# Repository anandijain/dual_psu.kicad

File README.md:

# diy modular synth in kicad

watch the video series where i build this!

https://www.youtube.com/playlist?list=PL79kqjVnD2ENdJDDSTUD3ZMdZPhVVu8yw

- psu completed, ready to print
- vca (needs to be redone)
- vco 

# todo
- vcf 
- envelope generator

build notes

* for the m2 standoffs i got, use 1/8 in holes and use the m3x12 screws into the acryllic and there is no need to countersink 
* to mount pots to the acryllic, drill 9/32 " holes 
* for 1/4" jack sockets use 3/8" holes

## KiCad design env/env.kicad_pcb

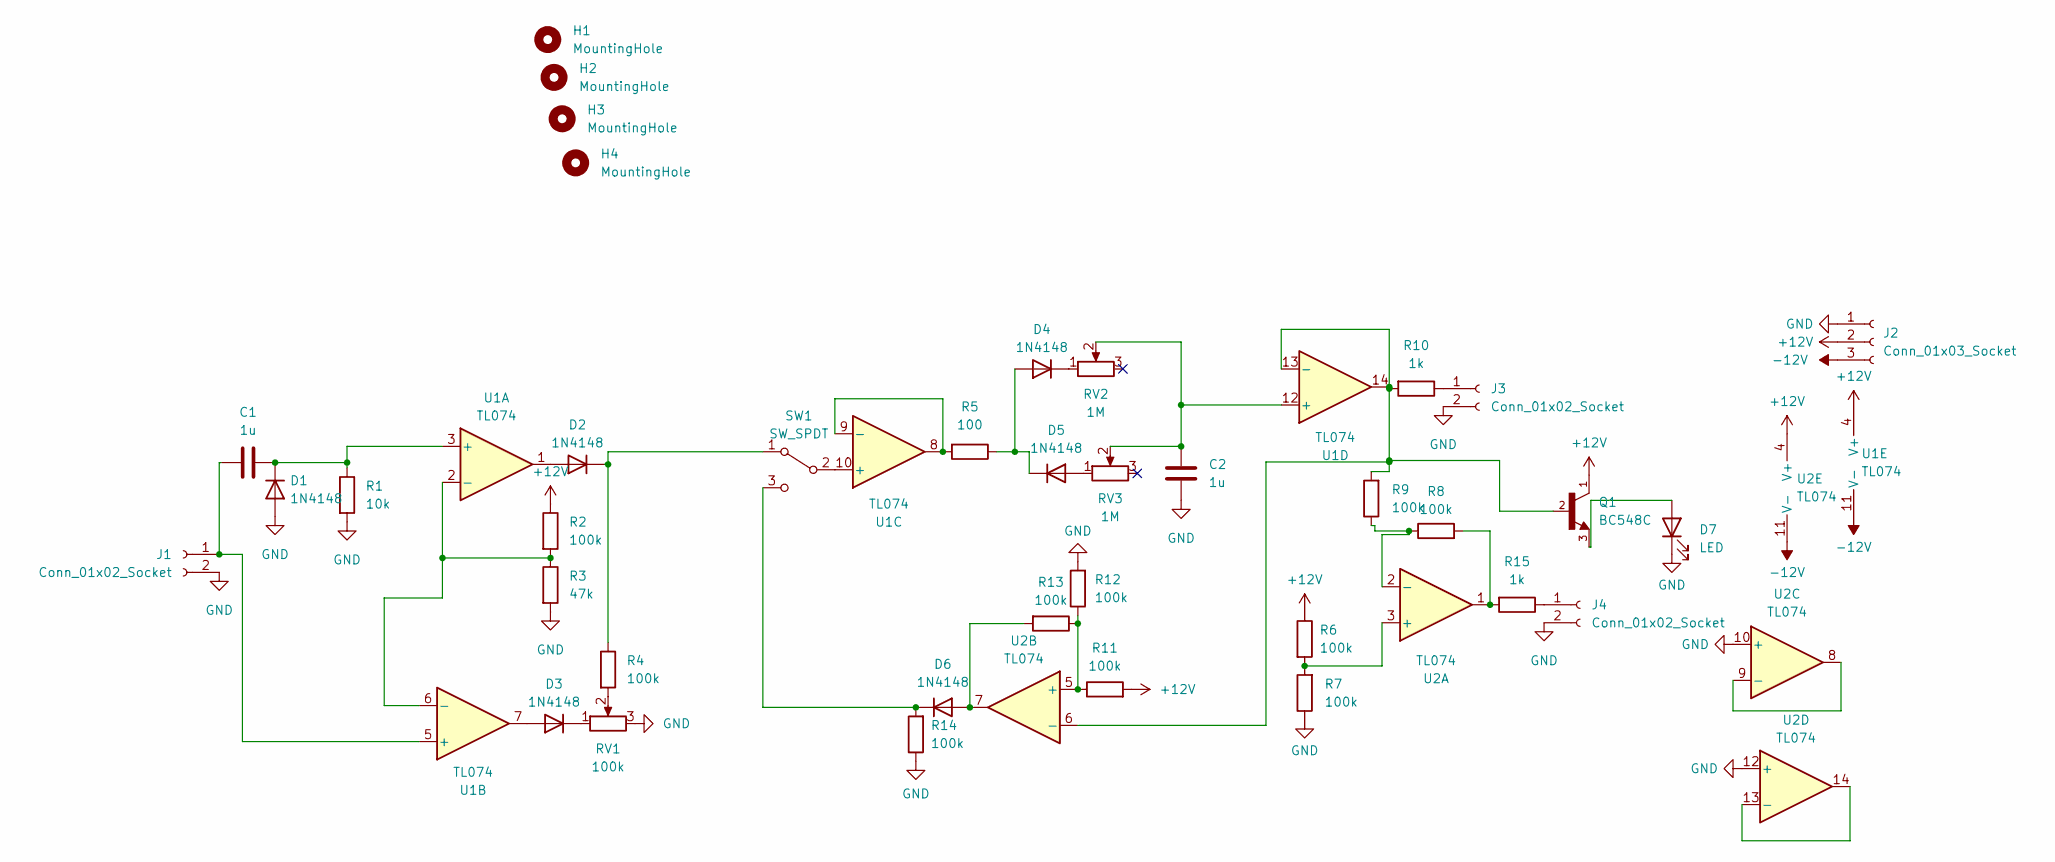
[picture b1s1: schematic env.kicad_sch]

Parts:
C1, C2: 1u; my_tht_cap
D1, D2, D3, D4, D5, D6: 1N4148; my_tht_diode
D7: LED; LED_D3.0mm
H1, H2, H3, H4: MountingHole; MountingHole_2.1mm
J1, J3, J4: Conn_01x02_Socket; my_really_cool_2pin
J2: Conn_01x03_Socket; my_really_cool_3pin
Q1: BC548C; my_bc548
R1: 10k; my_tht_r
R2, R4, R6, R7, R8, R9, R11, R12, R13, R14: 100k; my_tht_r
R3: 47k; my_tht_r
R5: 100; my_tht_r
R10, R15: 1k; my_tht_r
RV1: 100k; my_really_cool_3pin
RV2, RV3: 1M; my_really_cool_2pin
SW1: SW_SPDT; my_really_cool_3pin
U1, U2: TL074; my_dip14_no_f_pads

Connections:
+12V: J2.2, Q1.1, R2.1, R6.1, R11.2, U1.4 (V+), U2.4 (V+)
-12V: J2.3, U1.11 (V-), U2.11 (V-)
GND: C2.1, D1.2 (A), D7.1 (K), J1.2, J2.1, J3.2, J4.2, R1.2, R3.2, R7.1, R12.2, R14.1, RV1.3, U2.10 (+), U2.12 (+)
unnamed: C1.2, D1.1 (K), R1.1, U1.3 (+)
unnamed: D2.2 (A), U1.1
unnamed: D2.1 (K), R4.1, SW1.1 (A)
unnamed: D3.2 (A), U1.7
unnamed: D3.1 (K), RV1.1
unnamed: D4.2 (A), D5.1 (K), R5.1
unnamed: D4.1 (K), RV2.1
unnamed: D5.2 (A), RV3.1
unnamed: D6.2 (A), R13.2, U2.7
unnamed: D6.1 (K), R14.2, SW1.3 (C)
unnamed: D7.2 (A), Q1.3
unnamed: C1.1, J1.1, U1.5 (+)
unnamed: J3.1, R10.1
unnamed: J4.1, R15.1
unnamed: R4.2, RV1.2
unnamed: R8.2, R15.2, U2.1
unnamed: SW1.2 (B), U1.10 (+)
unnamed: R2.2, R3.1, U1.2 (-), U1.6 (-)
unnamed: R5.2, U1.8, U1.9 (-)
unnamed: C2.2, RV2.2, RV3.2, U1.12 (+)
unnamed: Q1.2, R9.2, R10.2, U1.13 (-), U1.14, U2.6 (-)
unnamed: R6.2, R7.2, U2.3 (+)
unnamed: R8.1, R9.1, U2.2 (-)
unnamed: R11.1, R12.1, R13.1, U2.5 (+)
unnamed: U2.8, U2.9 (-)
unnamed: U2.13 (-), U2.14

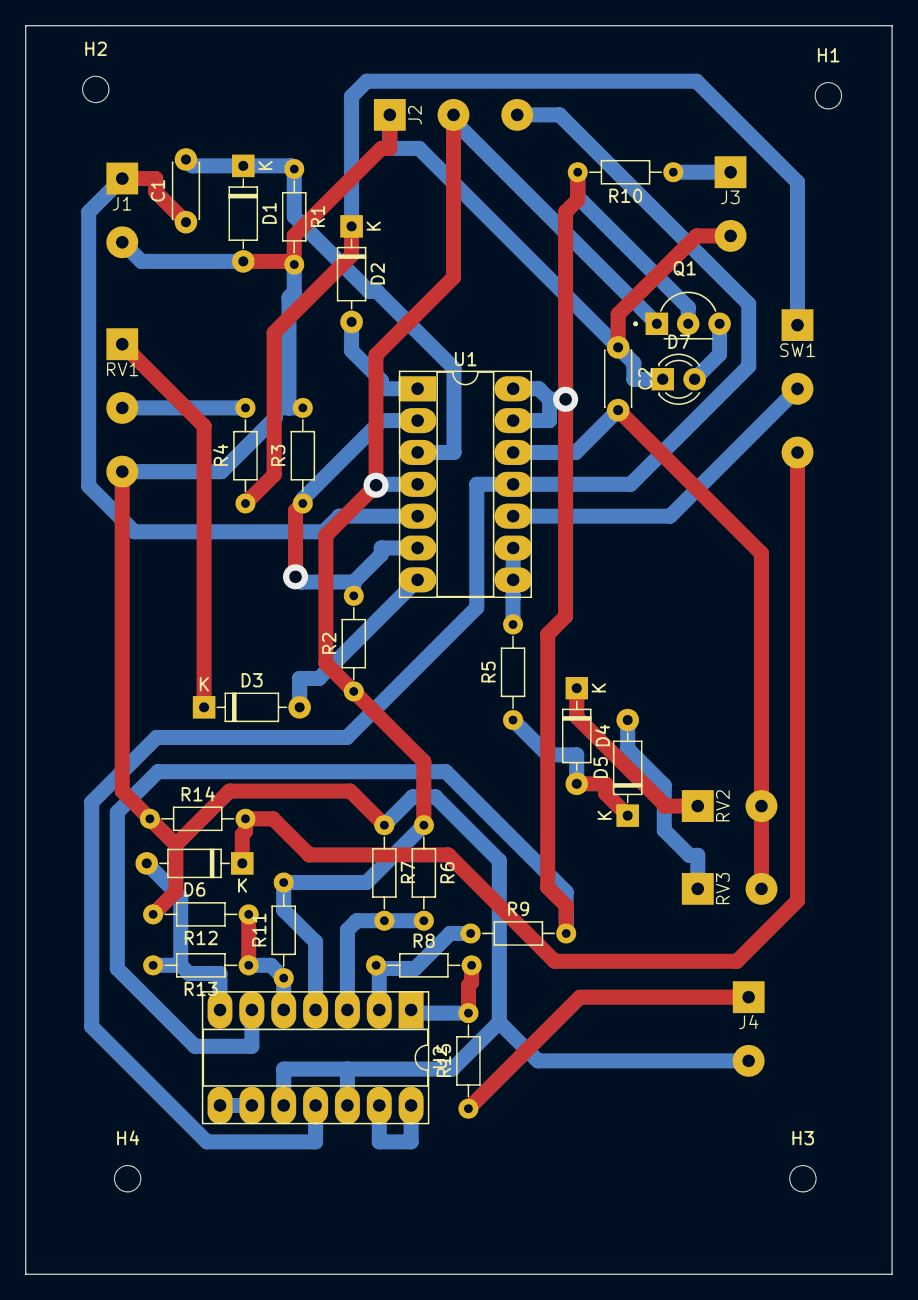
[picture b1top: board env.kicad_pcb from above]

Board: 2 copper layers, 69.1 x 99.6 mm, 39 parts (0 on the bottom side), 29 nets.

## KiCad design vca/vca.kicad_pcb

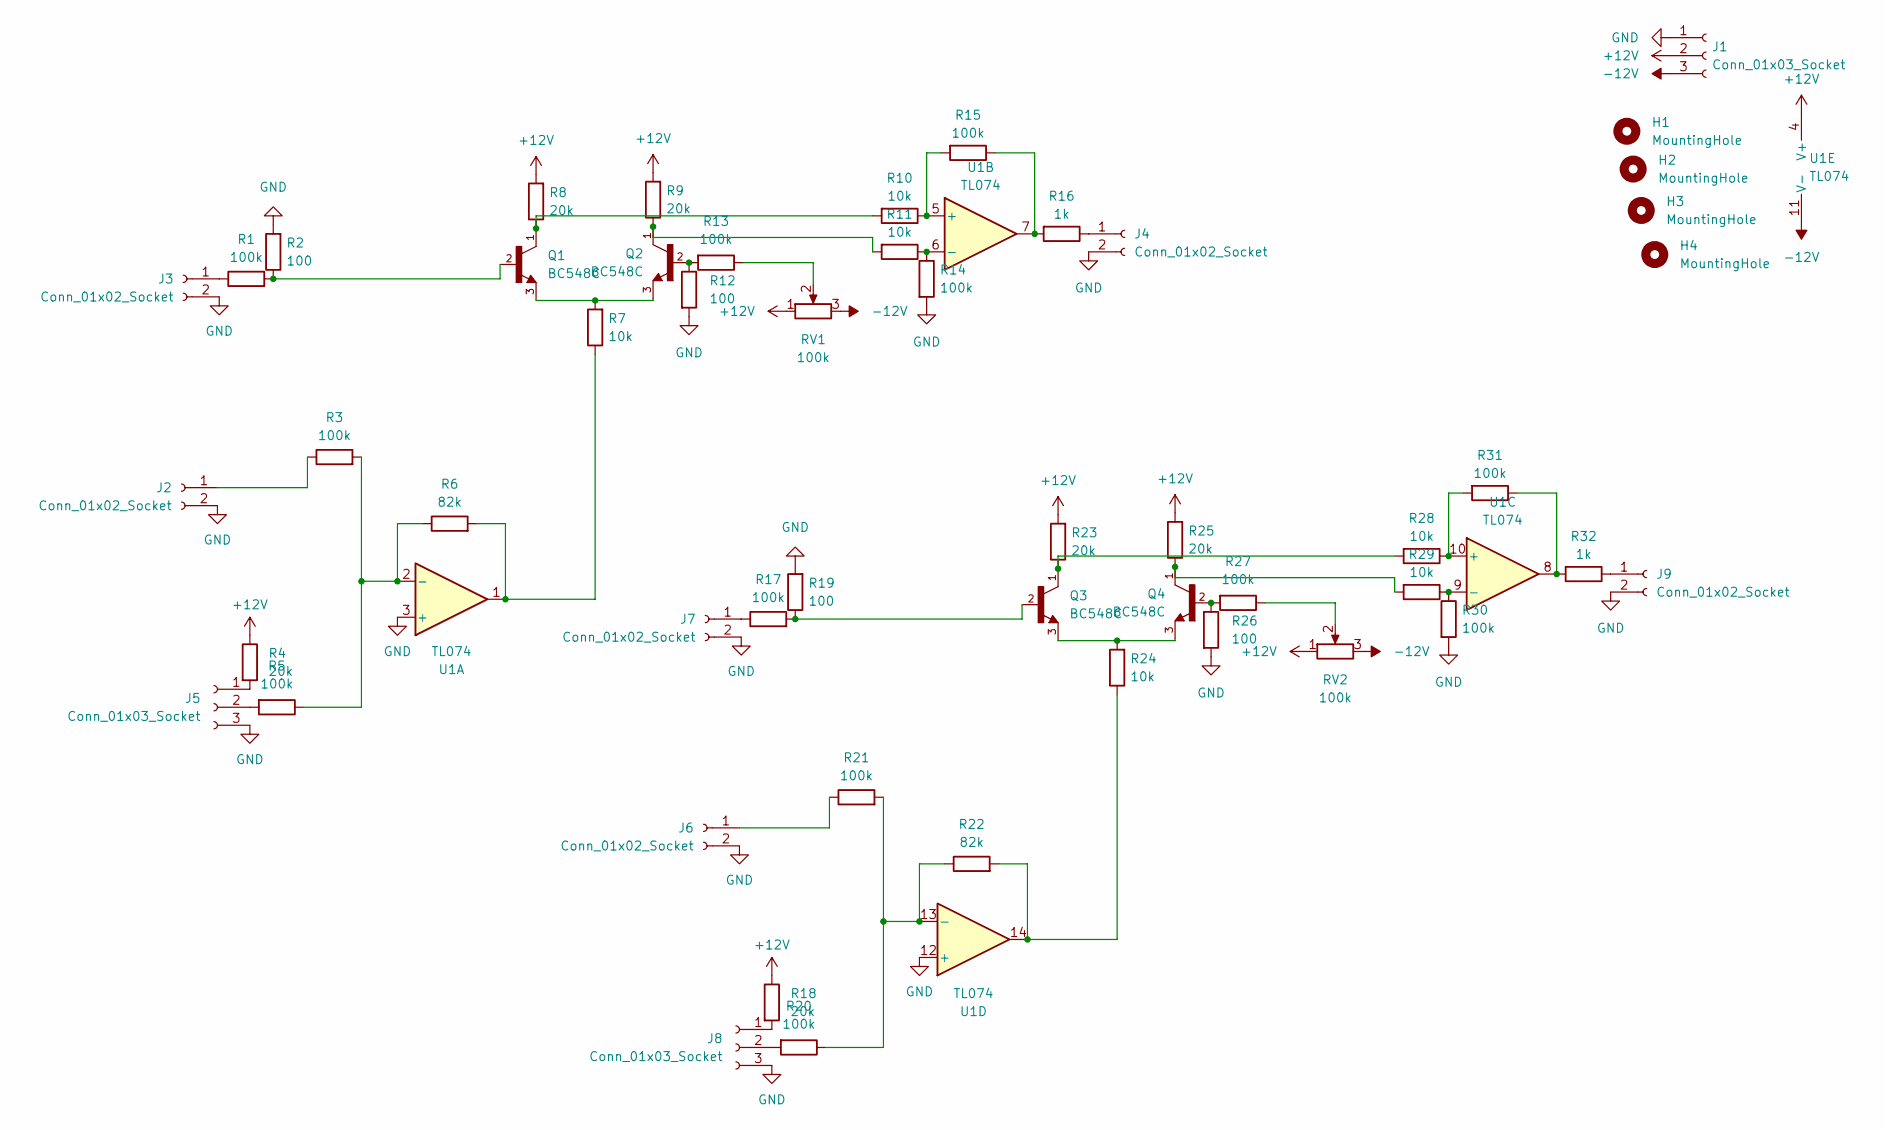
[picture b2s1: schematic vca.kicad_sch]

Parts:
H1, H2, H3, H4: MountingHole; MountingHole_2.1mm
J1, J5, J8: Conn_01x03_Socket; my_really_cool_3pin
J2, J3, J4, J6, J7, J9: Conn_01x02_Socket; my_really_cool_2pin
Q1, Q2, Q3, Q4: BC548C; my_bc548
R1, R3, R5, R13, R14, R15, R17, R20, R21, R27, R30, R31: 100k; my_tht_r
R2, R12, R19, R26: 100; my_tht_r
R4, R8, R9, R18, R23, R25: 20k; my_tht_r
R6, R22: 82k; my_tht_r
R7, R10, R11, R24, R28, R29: 10k; my_tht_r
R16, R32: 1k; my_tht_r
RV1, RV2: 100k; my_trimmer
U1: TL074; my_dip14_no_f_pads

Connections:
+12V: J1.2, R4.1, R8.2, R9.2, R18.1, R23.2, R25.2, RV1.1, RV2.1, U1.4 (V+)
-12V: J1.3, RV1.3, RV2.3, U1.11 (V-)
GND: J1.1, J2.2, J3.2, J4.2, J5.3, J6.2, J7.2, J8.3, J9.2, R2.2, R12.2, R14.2, R19.2, R26.2, R30.2, U1.3 (+), U1.12 (+)
unnamed: J2.1, R3.1
unnamed: J3.1, R1.1
unnamed: J4.1, R16.1
unnamed: J5.1, R4.2
unnamed: J5.2, R5.2
unnamed: J6.1, R21.1
unnamed: J7.1, R17.1
unnamed: J8.1, R18.2
unnamed: J8.2, R20.2
unnamed: J9.1, R32.1
unnamed: Q1.1, R8.1, R10.2
unnamed: Q1.2, R1.2, R2.1
unnamed: Q1.3, Q2.3, R7.2
unnamed: Q2.1, R9.1, R11.2
unnamed: Q2.2, R12.1, R13.2
unnamed: Q3.1, R23.1, R28.2
unnamed: Q3.2, R17.2, R19.1
unnamed: Q3.3, Q4.3, R24.2
unnamed: Q4.1, R25.1, R29.2
unnamed: Q4.2, R26.1, R27.2
unnamed: R6.2, R7.1, U1.1
unnamed: R13.1, RV1.2
unnamed: R15.1, R16.2, U1.7
unnamed: R22.2, R24.1, U1.14
unnamed: R27.1, RV2.2
unnamed: R31.1, R32.2, U1.8
unnamed: R3.2, R5.1, R6.1, U1.2 (-)
unnamed: R10.1, R15.2, U1.5 (+)
unnamed: R11.1, R14.1, U1.6 (-)
unnamed: R28.1, R31.2, U1.10 (+)
unnamed: R29.1, R30.1, U1.9 (-)
unnamed: R20.1, R21.2, R22.1, U1.13 (-)

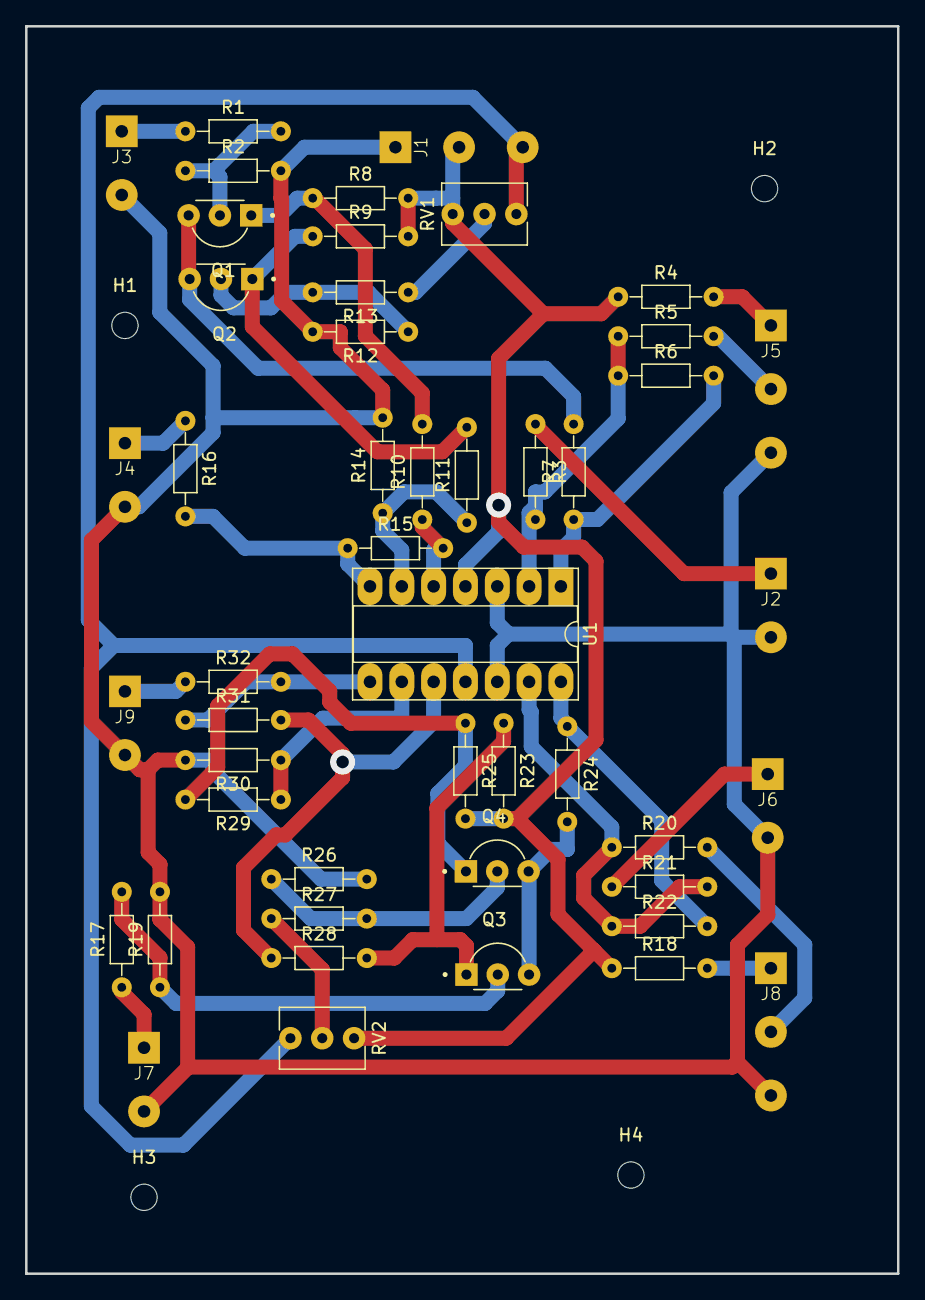
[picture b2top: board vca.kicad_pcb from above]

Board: 2 copper layers, 69.6 x 99.6 mm, 52 parts (0 on the bottom side), 35 nets.

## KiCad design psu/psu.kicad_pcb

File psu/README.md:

# psu.kicad

basic +-12v dual power supply from 12vac

designed to be done diy with ferric chloride (thick traces)

## Parts
- big caps https://www.amazon.com/dp/B08KTLQLVK
- -12v regulator https://www.digikey.com/en/products/detail/stmicroelectronics/L7912CV/585997
- +12v regulator https://www.digikey.com/en/products/detail/stmicroelectronics/L7812CV/585973
- diodes https://www.amazon.com/gp/product/B07Q5FZR7X
- small caps https://www.amazon.com/gp/product/B094HRK8QX/
- copper boards https://www.amazon.com/dp/B01MCVLDDZ

00:00:00 intro/materials
00:07:30 buffing board
00:10:00 tracing 
00:26:30 etching
00:42:30 rinse
01:01:00 how to not dremel
01:22:00 drilling
01:39:55 soldering

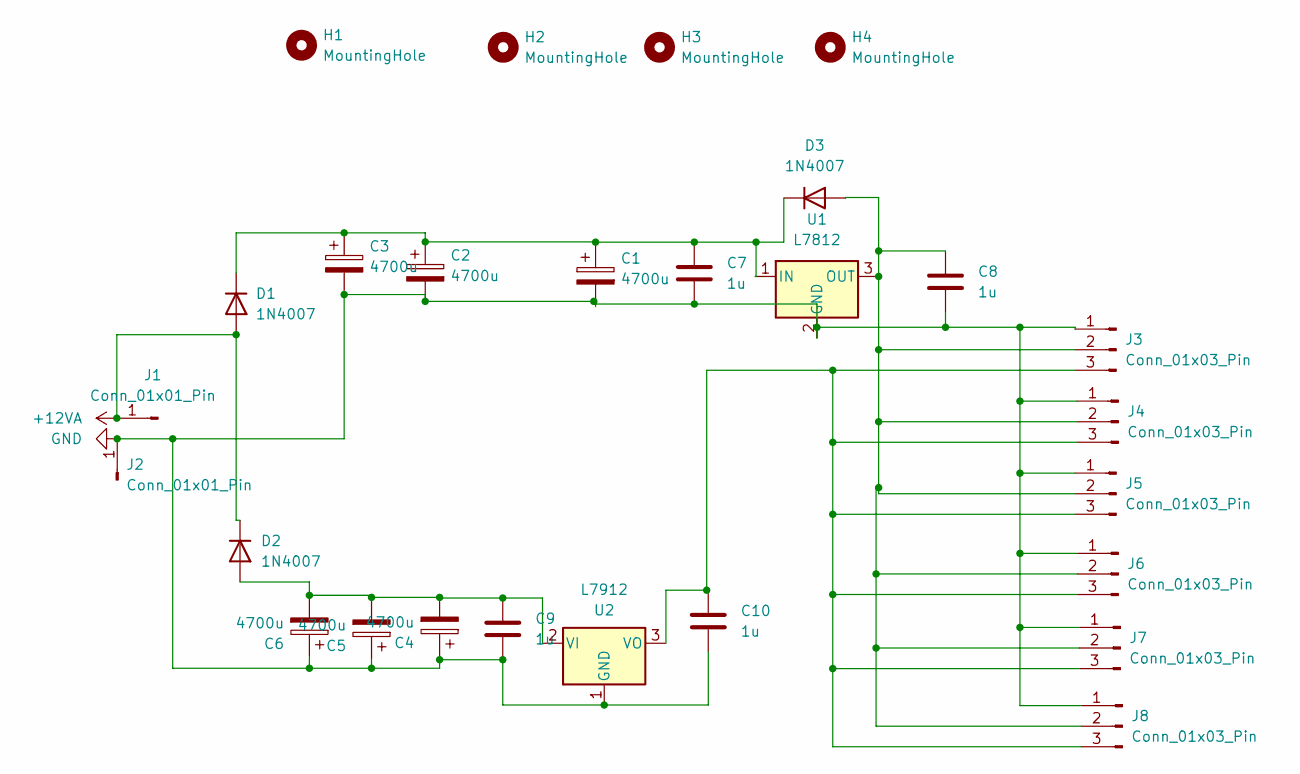
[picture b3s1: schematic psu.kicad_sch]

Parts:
C1, C2, C3, C4, C5, C6: 4700u; C_Radial_D18.0mm_H35.5mm_P7.50mm
C7, C8, C9, C10: 1u; C_Disc_D4.3mm_W1.9mm_P5.00mm
D1, D2, D3: 1N4007; D_DO-41_SOD81_P10.16mm_Horizontal
H1, H2, H3, H4: MountingHole; MountingHole_2.5mm
J1, J2: Conn_01x01_Pin; PinHeader_1x01_P2.54mm_Vertical
J3, J4, J5, J6, J7, J8: Conn_01x03_Pin; PinHeader_1x03_P2.54mm_Vertical
U1: L7812; TO-220-3_Vertical
U2: L7912; TO-220-3_Vertical

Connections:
+12VA: D1.2 (A), D2.1 (K), J1.1
GND: C1.2, C2.2, C3.2, C4.1, C5.1, C6.1, C7.2, C8.2, C9.2, C10.2, J2.1, J3.1, J4.1, J5.1, J6.1, J7.1, J8.1, U1.2 (GND), U2.1 (GND)
unnamed: C1.1, C2.1, C3.1, C7.1, D1.1 (K), D3.1 (K), U1.1 (IN)
unnamed: C4.2, C5.2, C6.2, C9.1, D2.2 (A), U2.2 (VI)
unnamed: C8.1, D3.2 (A), J3.2, J4.2, J5.2, J6.2, J7.2, J8.2, U1.3 (OUT)
unnamed: C10.1, J3.3, J4.3, J5.3, J6.3, J7.3, J8.3, U2.3 (VO)

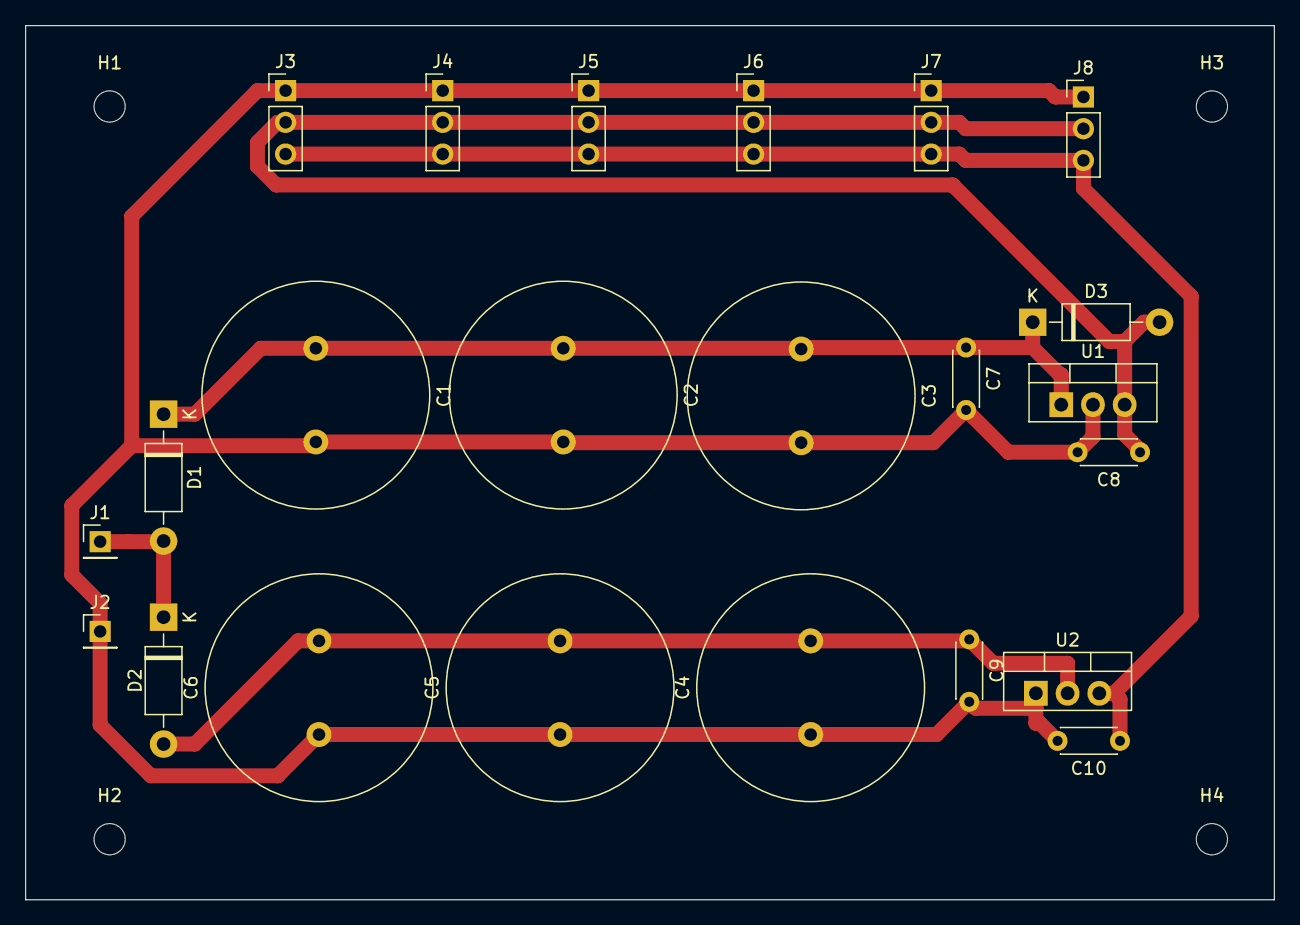
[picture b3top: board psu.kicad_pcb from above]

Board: 2 copper layers, 100.0 x 70.0 mm, 27 parts (0 on the bottom side), 6 nets.

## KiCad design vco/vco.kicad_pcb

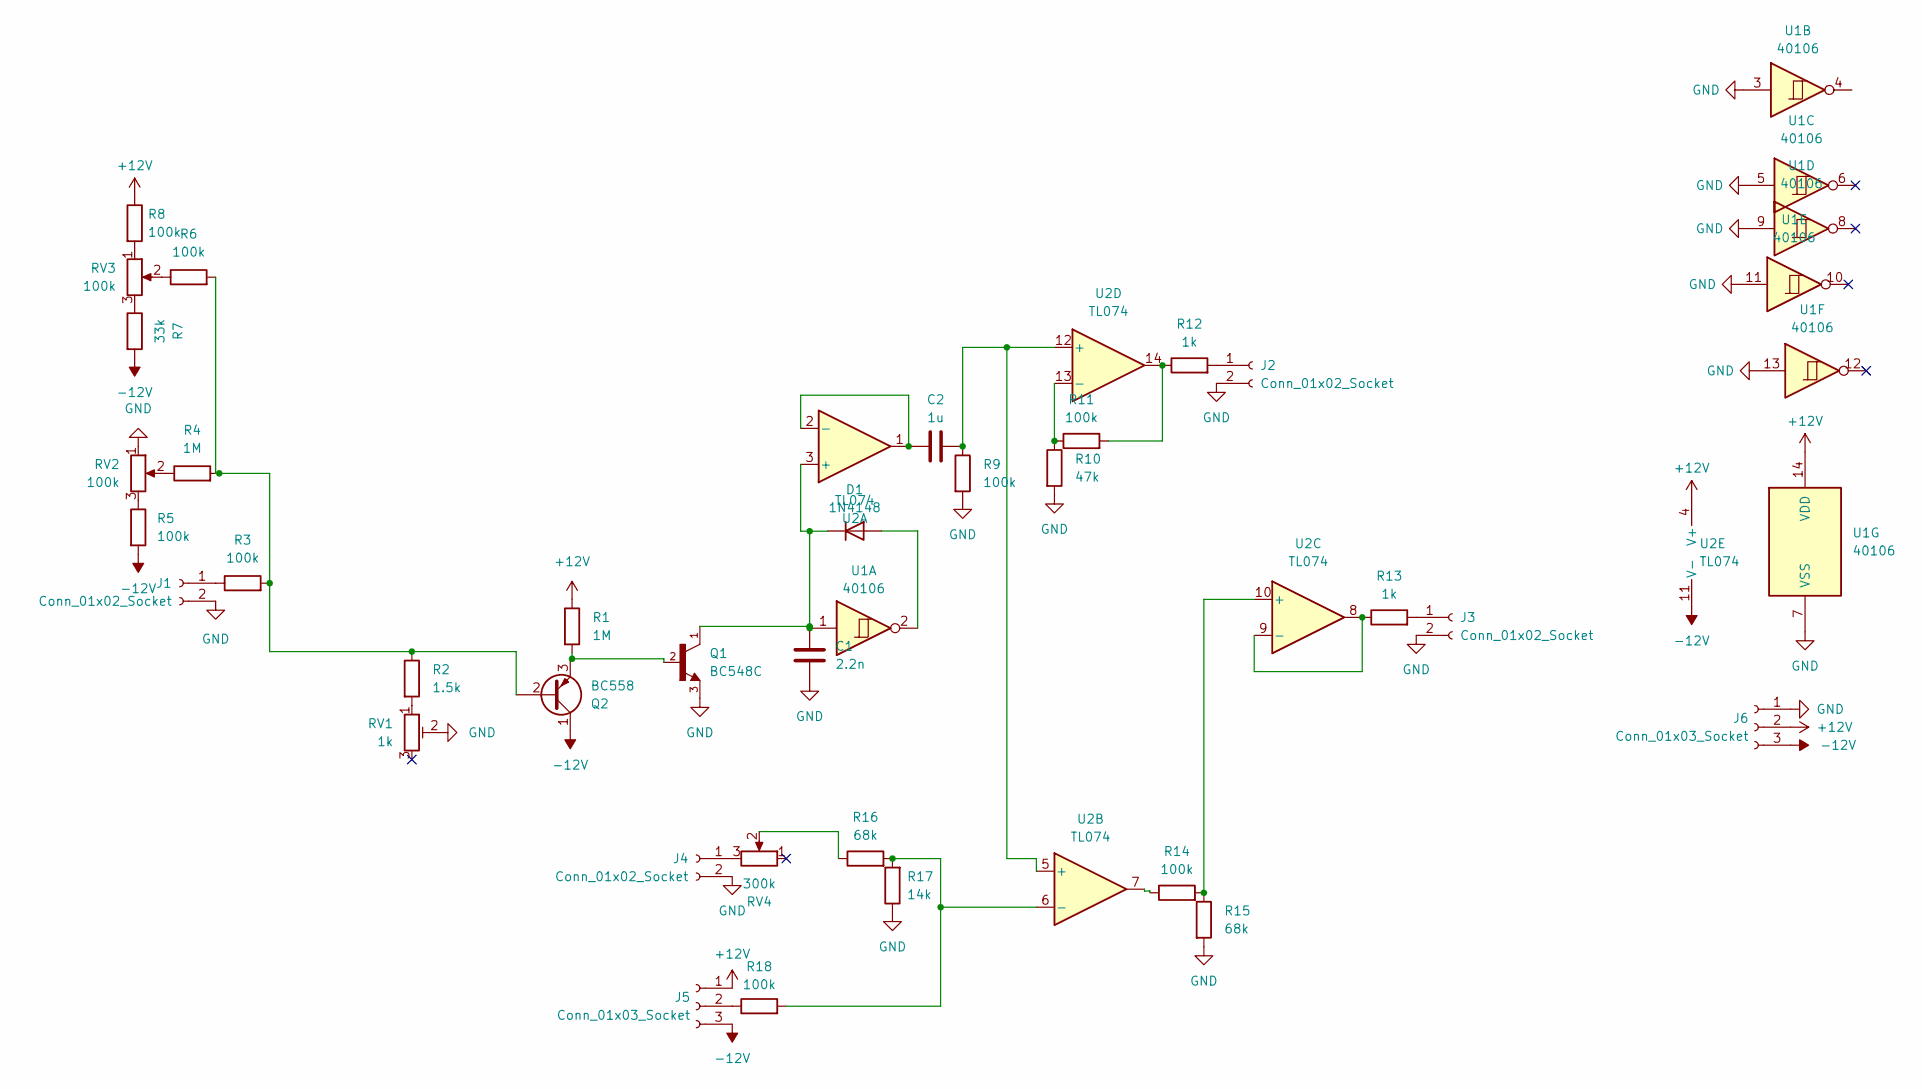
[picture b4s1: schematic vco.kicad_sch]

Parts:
C1: 2.2n; C_Disc_D7.5mm_W5.0mm_P7.50mm
C2: 1u; C_Disc_D7.5mm_W5.0mm_P7.50mm
D1: 1N4148; D_DO-35_SOD27_P7.62mm_Horizontal
J1, J2, J3, J4: Conn_01x02_Socket; PinSocket_1x02_P2.54mm_Vertical
J5, J6: Conn_01x03_Socket; PinSocket_1x03_P2.54mm_Vertical
Q1: BC548C; TO92250P510H770-3
Q2: BC558; TO-92_Inline_Wide
R1, R4: 1M; R_Axial_DIN0207_L6.3mm_D2.5mm_P10.16mm_Horizontal
R2: 1.5k; R_Axial_DIN0207_L6.3mm_D2.5mm_P10.16mm_Horizontal
R3, R5, R6, R8, R9, R11, R14, R18: 100k; R_Axial_DIN0207_L6.3mm_D2.5mm_P10.16mm_Horizontal
R7: 33k; R_Axial_DIN0207_L6.3mm_D2.5mm_P10.16mm_Horizontal
R10: 47k; R_Axial_DIN0207_L6.3mm_D2.5mm_P10.16mm_Horizontal
R12, R13: 1k; R_Axial_DIN0207_L6.3mm_D2.5mm_P10.16mm_Horizontal
R15, R16: 68k; R_Axial_DIN0207_L6.3mm_D2.5mm_P10.16mm_Horizontal
R17: 14k; R_Axial_DIN0207_L6.3mm_D2.5mm_P10.16mm_Horizontal
RV1: 1k; Potentiometer_Vishay_T73XW_Horizontal
RV2, RV3: 100k; Potentiometer_Runtron_RM-065_Vertical
RV4: 300k; Potentiometer_Runtron_RM-065_Vertical
U1: 40106; DIP-14_W7.62mm
U2: TL074; DIP-14_W7.62mm

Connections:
+12V: J5.1, J6.2, R1.1, R8.1, U1.14 (VDD), U2.4 (V+)
-12V: J5.3, J6.3, Q2.1 (C), R5.2, R7.2, U2.11 (V-)
GND: C1.2, J1.2, J2.2, J3.2, J4.2, J6.1, Q1.3, R9.2, R10.2, R15.2, R17.1, RV1.2, RV2.1, U1.3, U1.5, U1.7 (VSS), U1.9, U1.11, U1.13
unnamed: D1.2 (A), U1.2
unnamed: C1.1, D1.1 (K), Q1.1, U1.1, U2.3 (+)
unnamed: J1.1, R3.1
unnamed: J2.1, R12.2
unnamed: J3.1, R13.2
unnamed: J4.1, RV4.3
unnamed: Q2.2 (B), R2.1, R3.2, R4.2, R6.2
unnamed: Q1.2, Q2.3 (E), R1.2
unnamed: R2.2, RV1.1
unnamed: R4.1, RV2.2
unnamed: R5.1, RV2.3
unnamed: R6.1, RV3.2
unnamed: R7.1, RV3.3
unnamed: R8.2, RV3.1
unnamed: R11.2, R12.1, U2.14
unnamed: R14.1, U2.7
unnamed: R16.1, RV4.2
unnamed: C2.1, U2.1, U2.2 (-)
unnamed: C2.2, R9.1, U2.5 (+), U2.12 (+)
unnamed: R14.2, R15.1, U2.10 (+)
unnamed: R13.1, U2.8, U2.9 (-)
unnamed: R10.1, R11.1, U2.13 (-)

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
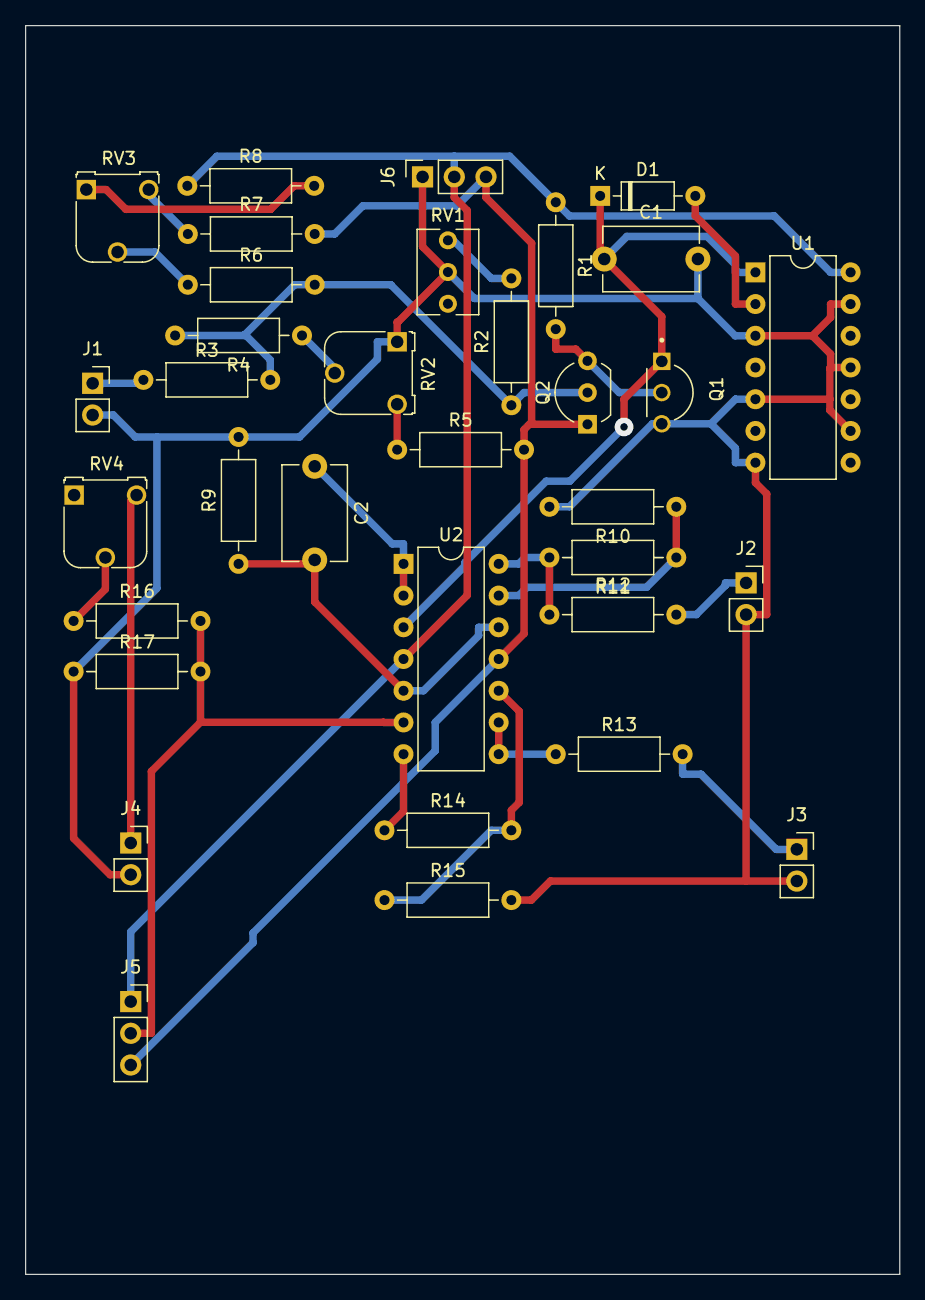
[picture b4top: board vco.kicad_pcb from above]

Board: 2 copper layers, 70.0 x 100.0 mm, 34 parts (0 on the bottom side), 26 nets.

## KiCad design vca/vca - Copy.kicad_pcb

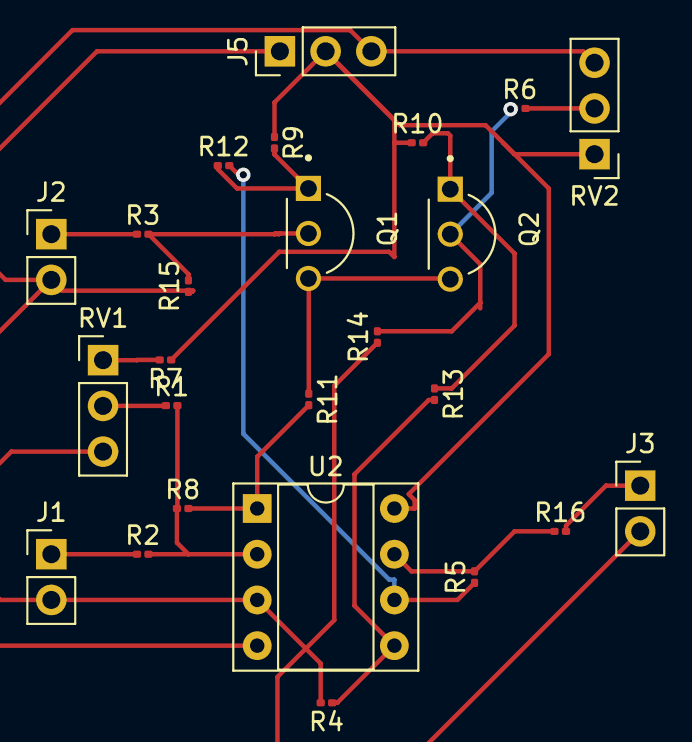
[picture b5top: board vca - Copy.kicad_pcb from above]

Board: 2 copper layers, 25 parts (0 on the bottom side), 19 nets.

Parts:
J1, J2, J3: Conn_01x02_Socket; PinHeader_1x02_P2.54mm_Vertical
J5: Conn_01x03_Socket; PinHeader_1x03_P2.54mm_Vertical
Q1, Q2: BC548C; TO92250P510H770-3
R1, R2, R3, R4, R5, R6: 100K; R_0201_0603Metric
R7, R9, R10: 20K; R_0201_0603Metric
R8: 82K; R_0201_0603Metric
R11, R12, R13: 10K; R_0201_0603Metric
R14, R15: 100; R_0201_0603Metric
R16: 1K; R_0201_0603Metric
RV1, RV2: 100K; PinHeader_1x03_P2.54mm_Vertical
U2: TL072; DIP-8_W7.62mm_Socket

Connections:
+12V: J5.2, R7.1, R9.1, R10.1, RV2.1, U2.8 (V+)
-12V: J5.3, RV2.3, U2.4 (V-)
GND: J1.2, J2.2, J3.2, J5.1, R4.2, R14.1, R15.1, RV1.3, U2.3 (+)
unnamed: J1.1, R2.1
unnamed: J2.1, R3.1
unnamed: J3.1, R16.2
unnamed: Q1.1, R9.2, R12.1
unnamed: Q1.2, R3.2, R15.2
unnamed: Q1.3, Q2.3, R11.1
unnamed: Q2.1, R10.2, R13.2
unnamed: Q2.2, R6.1, R14.2
unnamed: R1.1, RV1.2
unnamed: R6.2, RV2.2
unnamed: R7.2, RV1.1
unnamed: R8.2, R11.2, U2.1
unnamed: R5.2, R16.1, U2.7
unnamed: R1.2, R2.2, R8.1, U2.2 (-)
unnamed: R4.1, R13.1, U2.5 (+)
unnamed: R5.1, R12.2, U2.6 (-)

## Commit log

2023-12-28 init
2023-12-28 image
2023-12-29 add a vca move things around
2024-01-01 add vco remove zips
2024-01-01 increase track width and clearance + reroute
2024-01-01 increase via size
2024-01-03 fix missing resistor add link to yt add vco bom
2024-01-04 add psu bom, improve trace width
2024-01-08 add the eg and reroute the vca.
2024-01-08 turn vca to dual vca add mounting holes
2024-01-08 use custom footprints with bigger pads
2024-01-08 update almost all other footprints to fatty pads
2024-01-12 FRIENDSHIP ENDED WITH PACKAGE_DIP. added a keep-out on F.cu for dip14
2024-01-14 some notes about front panel construction and some boms
